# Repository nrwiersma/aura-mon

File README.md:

<picture>
  <source media="(prefers-color-scheme: dark)" srcset="http://svg.wiersma.co.za/github/project.v2?title=aura mon&tag=energy%20data%20logger&mode=dark">
  <source media="(prefers-color-scheme: light)" srcset="http://svg.wiersma.co.za/github/project.v2?title=aura mon&tag=energy%20data%20logger">
  
</picture>

`Aura Mon` is an RP2350-based energy data logger built around the tiny [SPM01](https://www.bituo-technik.com/product/spm01-flexible-1pn-63a/) Modbus meter. It samples power data over RS485, stores it on an SD card, and serves a local HTTP API and web UI over Ethernet.

## At a glance

* RP2350 microcontroller
* Modbus RTU over RS485 (SPM01)
* Ethernet for reliable network connectivity
* SD card logging and static web UI hosting
* RTC for timestamped data
* HTTP API with OTA updates and metrics

## System overview

## Data flow

## Why

The goal of this project is to create a reliable and easy-to-use energy data logger that can be used to monitor energy consumption in a home or small business. The SPM01 is a very affordable energy meter that can measure voltage, current, power, energy, and power factor while fitting in tight electrical panels.

## Quick start

1. Assemble the board and connect the SPM01 to the RS485 terminals.
2. Insert an SD card (required for logging).
3. Power the board with a regulated 5V supply on the screw terminals (or via USB-C with the jumper fitted for testing).
4. Connect Ethernet and find the device IP via your router's DHCP lease table.
5. Open `http://<device-ip>` to view the UI and use the API.

## Firmware

The firmware lives in `firmware/` and is written in C++ using the Arduino framework.

* Build/flash instructions: `firmware/FIRMWARE.md`
* HTTP API reference: `firmware/API.md`

### API highlights

* `GET /status` for live readings and runtime stats.
* `GET /energy` for CSV data export.
* `GET /logs` for log streaming.
* `GET`/`POST /config` for device configuration.
* `POST /ota` for firmware updates.
* `GET /metrics` for Prometheus-style metrics.

## Powering

The board can be powered using an external 5V power supply connected to the screw terminals. For testing purposes, it can also be powered via USB-C after connecting the onboard jumper.

## Safety

> [!WARNING]
> This project interfaces with mains-connected equipment. Only install it if you are qualified and follow local electrical safety requirements.

## Project status

The firmware and hardware are still in development and are only tested on the author's hardware. Expect rough edges and please report issues or improvements.

## Changelog

#### v0.1.0

* Initial schematic and board
* Initial firmware with basic functionality to read from the SPM01 and store data on the SD card

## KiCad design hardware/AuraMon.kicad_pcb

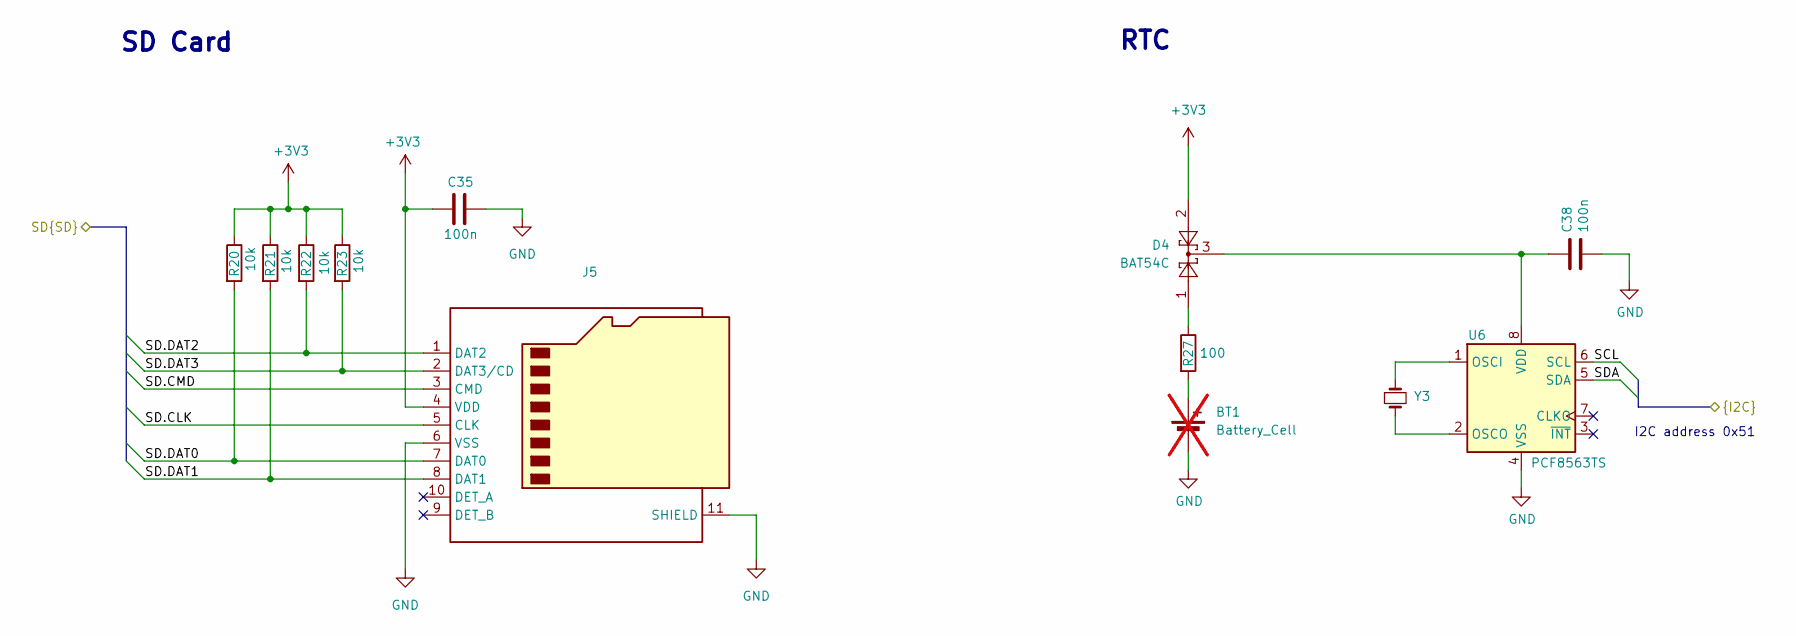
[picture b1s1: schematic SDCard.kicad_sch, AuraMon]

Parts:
BT1: Battery_Cell; BatteryHolder_Keystone_1060_1x2032; not fitted
C35, C38: 100n; C_0402_1005Metric; MPN CL05B104KO5NNNC; JLCPCB Part # C1525
D4: BAT54C; SOT-23; MPN BAT54C-7-F; JLCPCB Part # C134405
J5: Micro_SD_Card_Det_Hirose_DM3AT; AMPHENOL_1140084168; MPN 114-00841-68; JLCPCB Part # C3195424
R20, R21, R22, R23: 10k; R_0402_1005Metric; MPN RC0402JR-0710KL; JLCPCB Part # C60489
R27: 100; R_0402_1005Metric; MPN RC0402FR-07100RL; JLCPCB Part # C106232
U6: PCF8563TS; MSOP-8_3x3mm_P0.65mm; MPN PCF85063ATT/AJ; JLCPCB Part # C165608
Y3: X321532768KGD2SI; Crystal_SMD_3215-2Pin_3.2x1.5mm; MPN X321532768KGD2SI; JLCPCB Part # C620155

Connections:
+3V3: C35.2, D4.2, J5.4 (VDD), R20.1, R21.1, R22.1, R23.1; also elsewhere on the board
/MCU/SCL: U6.6 (SCL); also elsewhere on the board
/MCU/SD.CLK: J5.5 (CLK); also elsewhere on the board
/MCU/SD.CMD: J5.3 (CMD); also elsewhere on the board
/MCU/SD.DAT0: J5.7 (DAT0), R20.2; also elsewhere on the board
/MCU/SD.DAT1: J5.8 (DAT1), R21.2; also elsewhere on the board
/MCU/SD.DAT2: J5.1 (DAT2), R22.2; also elsewhere on the board
/MCU/SD.DAT3: J5.2 (DAT3/CD), R23.2; also elsewhere on the board
/MCU/SDA: U6.5 (SDA); also elsewhere on the board
GND: BT1.2 (-), C35.1, C38.2, J5.6 (VSS), J5.11 (SHIELD), U6.4 (VSS); also elsewhere on the board
unnamed: BT1.1 (+), R27.2
unnamed: D4.1, R27.1
unnamed: U6.1 (OSCI), Y3.1
unnamed: U6.2 (OSCO), Y3.2
unnamed: C38.1, D4.3, U6.8 (VDD)

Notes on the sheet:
I2C address 0x51
RTC
SD Card

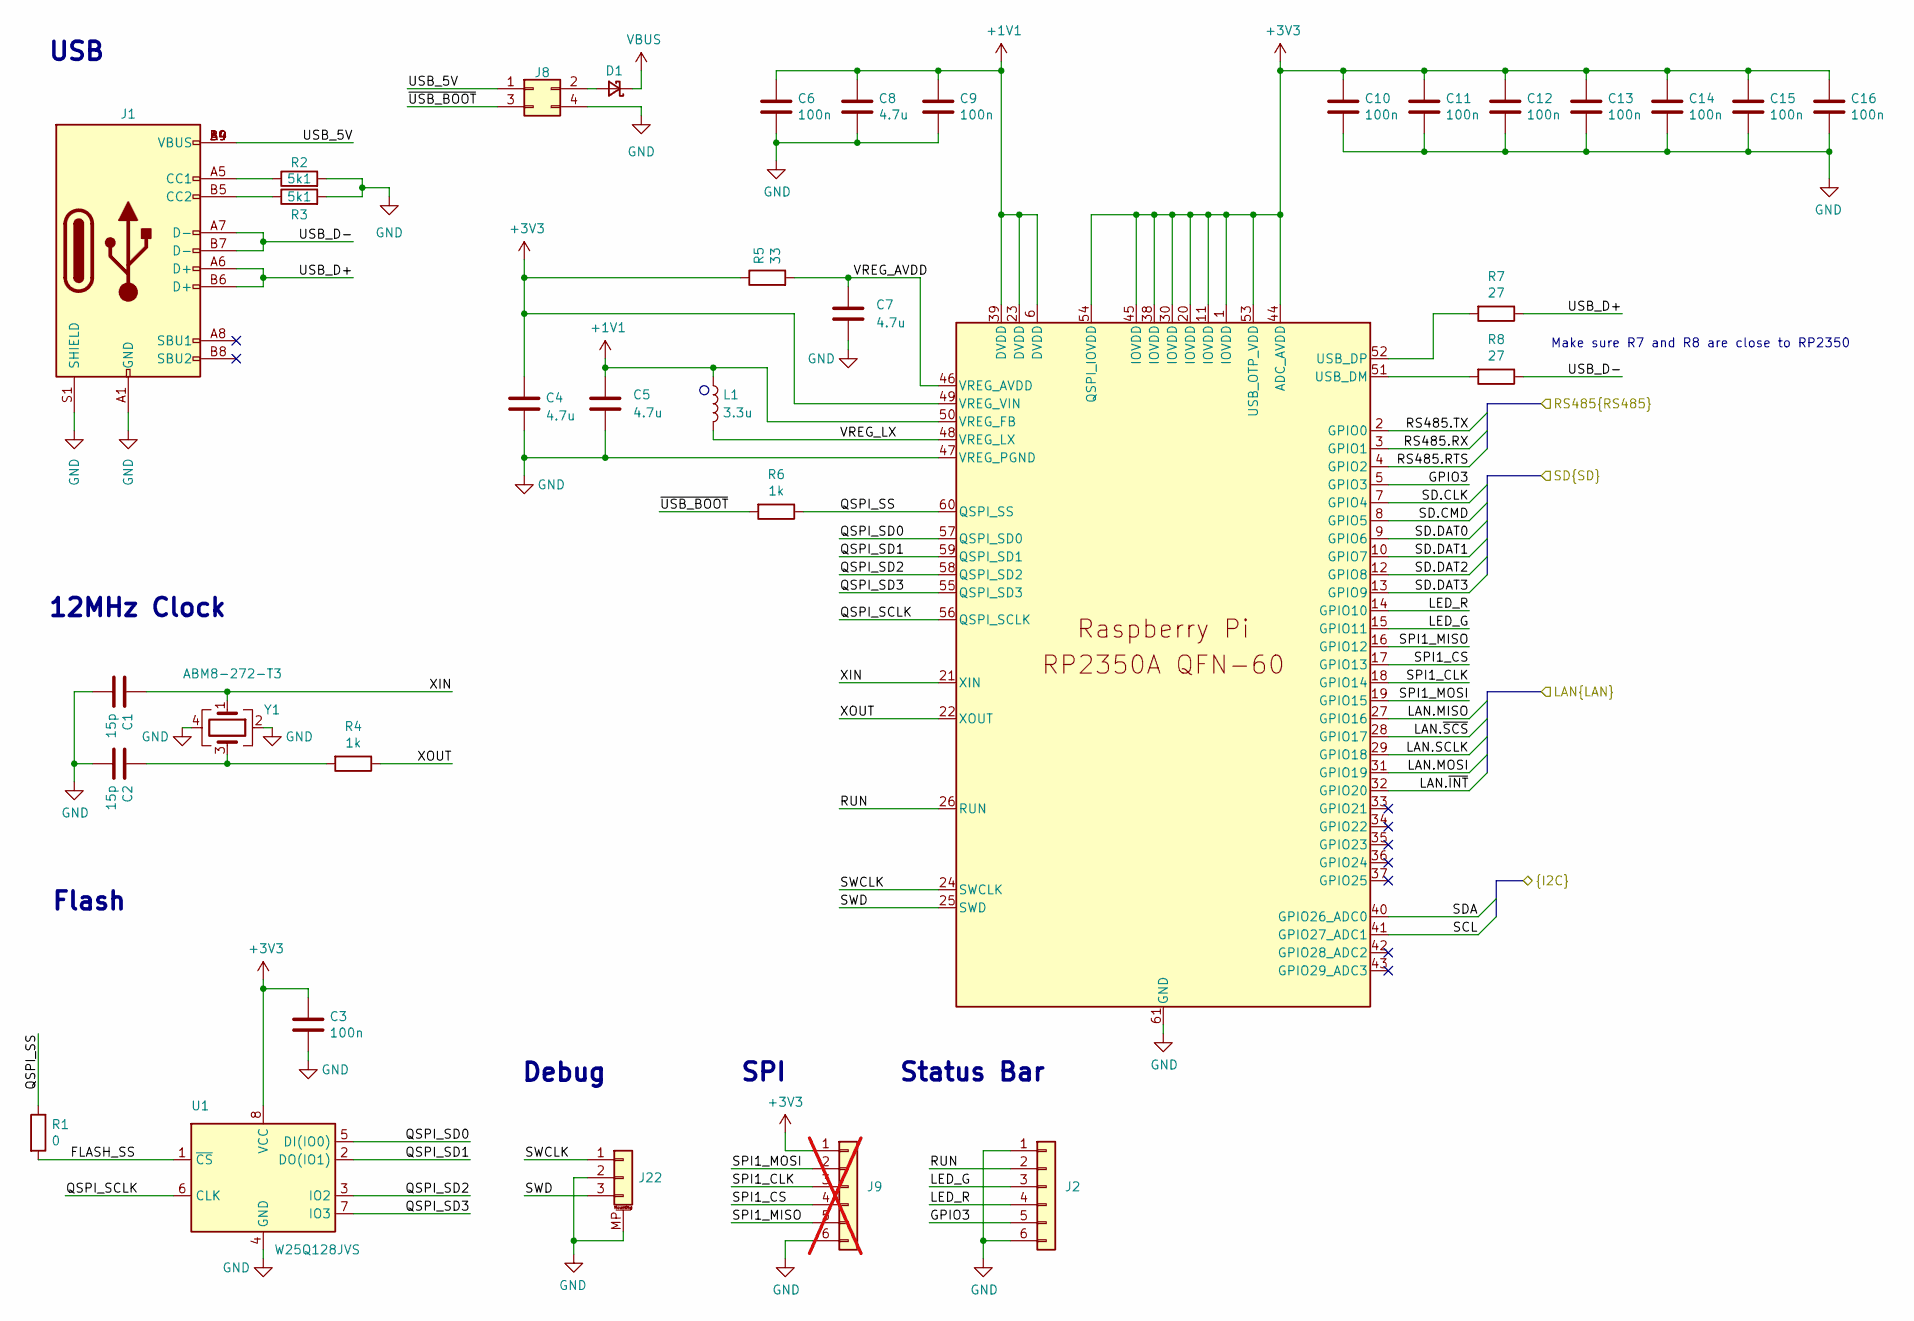
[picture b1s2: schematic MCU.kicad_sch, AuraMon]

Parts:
C1, C2: 15p; C_0402_1005Metric; MPN CL05C150JB5NNNC; JLCPCB Part # C86285
C3, C6, C9, C10, C11, C12, C13, C14, C15, C16: 100n; C_0402_1005Metric; MPN CL05B104KO5NNNC; JLCPCB Part # C1525
C4, C5: 4.7u; C_0402_1005Metric_small_pads; MPN CL05A475MO5NUNC; JLCPCB Part # C318563
C7, C8: 4.7u; C_0402_1005Metric; MPN CL05A475MO5NUNC; JLCPCB Part # C318563
D1: D_Schottky_Small; D_SOD-323; MPN BAT760-7; JLCPCB Part # C124187
J1: USB_C_Receptacle_USB2.0_16P; USB-C-SMD_TYPEC-305-ACP16H458; MPN TYPEC-305-ACP16H458; JLCPCB Part # C5454943
J2: Conn_01x06; JST_SH_BM06B-SRSS-TB_1x06-1MP_P1.00mm_Vertical; MPN BM06B-SRSS-TB(LF)(SN); JLCPCB Part # C160392
J8: Conn_02x02_Odd_Even; PinHeader_2x02_P1.27mm_Vertical; MPN DW127R-22-04-23; JLCPCB Part # C2935950
J9: Conn_01x06; JST_SUR_BM06B-SURS-TF_1x06-1MP_P0.80mm_Vertical; not fitted
J22: SM03B-SRSS-TB; JST_SH_SM03B-SRSS-TB_1x03-1MP_P1.00mm_Horizontal
L1: 3.3u; L_pol_2016; MPN AOTA-B201610S3R3-101-T; JLCPCB Part # C42411119
R1: 0; R_0402_1005Metric; MPN RC0402JR-070RL; JLCPCB Part # C60485
R2, R3: 5k1; R_0402_1005Metric; MPN RC0402FR-075K1L; JLCPCB Part # C105872
R4, R6: 1k; R_0402_1005Metric; MPN RC0402FR-071KL; JLCPCB Part # C106235
R5: 33; R_0402_1005Metric; MPN RC0402FR-0733RL; JLCPCB Part # C138002
R7, R8: 27; R_0402_1005Metric; MPN RC0402FR-0727RL; JLCPCB Part # C138021
U1: W25Q128JVS; SOIC-8_5.23x5.23mm_P1.27mm; MPN W25Q128JVSIQ; JLCPCB Part # C97521
U2: RP2350A; QFN-60_7X7_RPI; MPN RP2350A; JLCPCB Part # C42411118
Y1: ABM8-272-T3; Crystal_SMD_3225-4Pin_3.2x2.5mm; MPN ABM8-272-T3; JLCPCB Part # C20625731

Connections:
+1V1: C5.1, C6.1, C8.1, C9.1, L1.1, U2.6 (DVDD), U2.23 (DVDD), U2.39 (DVDD), U2.50 (VREG_FB)
+3V3: C3.1, C4.1, C10.1, C11.1, C12.1, C13.1, C14.1, C15.1, C16.1, J9.1, R5.1, U1.8 (VCC), U2.1 (IOVDD), U2.11 (IOVDD), U2.20 (IOVDD), U2.30 (IOVDD), U2.38 (IOVDD), U2.44 (ADC_AVDD), U2.45 (IOVDD), U2.49 (VREG_VIN), U2.53 (USB_OTP_VDD), U2.54 (QSPI_IOVDD); also elsewhere on the board
/LAN/LAN.MISO: U2.27 (GPIO16); also elsewhere on the board
/LAN/LAN.MOSI: U2.31 (GPIO19); also elsewhere on the board
/LAN/LAN.SCLK: U2.29 (GPIO18); also elsewhere on the board
/LAN/LAN.~INT: U2.32 (GPIO20); also elsewhere on the board
/LAN/LAN.~SCS: U2.28 (GPIO17); also elsewhere on the board
/MCU/FLASH_SS: R1.2, U1.1 (~CS)
/MCU/GPIO3: J2.5, U2.5 (GPIO3)
/MCU/LED_G: J2.3, U2.15 (GPIO11)
/MCU/LED_R: J2.4, U2.14 (GPIO10)
/MCU/QSPI_SCLK: U1.6 (CLK), U2.56 (QSPI_SCLK)
/MCU/QSPI_SD0: U1.5 (DI(IO0)), U2.57 (QSPI_SD0)
/MCU/QSPI_SD1: U1.2 (DO(IO1)), U2.59 (QSPI_SD1)
/MCU/QSPI_SD2: U1.3 (IO2), U2.58 (QSPI_SD2)
/MCU/QSPI_SD3: U1.7 (IO3), U2.55 (QSPI_SD3)
/MCU/QSPI_SS: R1.1, R6.1, U2.60 (QSPI_SS)
/MCU/RS485.RTS: U2.4 (GPIO2); also elsewhere on the board
/MCU/RS485.RX: U2.3 (GPIO1); also elsewhere on the board
/MCU/RS485.TX: U2.2 (GPIO0); also elsewhere on the board
/MCU/RUN: J2.2, U2.26 (RUN)
/MCU/SCL: U2.41 (GPIO27_ADC1); also elsewhere on the board
/MCU/SD.CLK: U2.7 (GPIO4); also elsewhere on the board
/MCU/SD.CMD: U2.8 (GPIO5); also elsewhere on the board
/MCU/SD.DAT0: U2.9 (GPIO6); also elsewhere on the board
/MCU/SD.DAT1: U2.10 (GPIO7); also elsewhere on the board
/MCU/SD.DAT2: U2.12 (GPIO8); also elsewhere on the board
/MCU/SD.DAT3: U2.13 (GPIO9); also elsewhere on the board
/MCU/SDA: U2.40 (GPIO26_ADC0); also elsewhere on the board
/MCU/SPI1_CLK: J9.3, U2.18 (GPIO14)
/MCU/SPI1_CS: J9.4, U2.17 (GPIO13)
/MCU/SPI1_MISO: J9.5, U2.16 (GPIO12)
/MCU/SPI1_MOSI: J9.2, U2.19 (GPIO15)
/MCU/SWCLK: J22.1, U2.24 (SWCLK)
/MCU/SWD: J22.3, U2.25 (SWD)
/MCU/USB_5V: J1.A4 (VBUS), J1.A9 (VBUS), J1.B4 (VBUS), J1.B9 (VBUS), J8.1
/MCU/USB_D+: J1.A6 (D+), J1.B6 (D+), R7.1
/MCU/USB_D-: J1.A7 (D-), J1.B7 (D-), R8.1
/MCU/VREG_AVDD: C7.1, R5.2, U2.46 (VREG_AVDD)
/MCU/VREG_LX: L1.2, U2.48 (VREG_LX)
/MCU/XIN: C1.1, U2.21 (XIN), Y1.1
/MCU/XOUT: R4.1, U2.22 (XOUT)
/MCU/~USB_BOOT: J8.3, R6.2
GND: C1.2, C2.2, C3.2, C4.2, C5.2, C6.2, C7.2, C8.2, C9.2, C10.2, C11.2, C12.2, C13.2, C14.2, C15.2, C16.2, J1.A1 (GND), J1.A12 (GND), J1.B1 (GND), J1.B12 (GND), J1.S1 (SHIELD), J2.1, J2.6, J8.4, J9.6, J22.2, J22.MP (MountPin), R2.2, R3.2, U1.4 (GND), U2.47 (VREG_PGND), U2.61 (GND), Y1.2, Y1.4; also elsewhere on the board
unnamed: C2.1, R4.2, Y1.3
unnamed: D1.2 (A), J8.2
unnamed: J1.A5 (CC1), R2.1
unnamed: J1.B5 (CC2), R3.1
unnamed: R8.2, U2.51 (USB_DM)
unnamed: R7.2, U2.52 (USB_DP)
VBUS: D1.1 (K); also elsewhere on the board

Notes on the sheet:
Debug
Status Bar
USB
Make sure R7 and R8 are close to RP2350
SPI
12MHz Clock
Flash

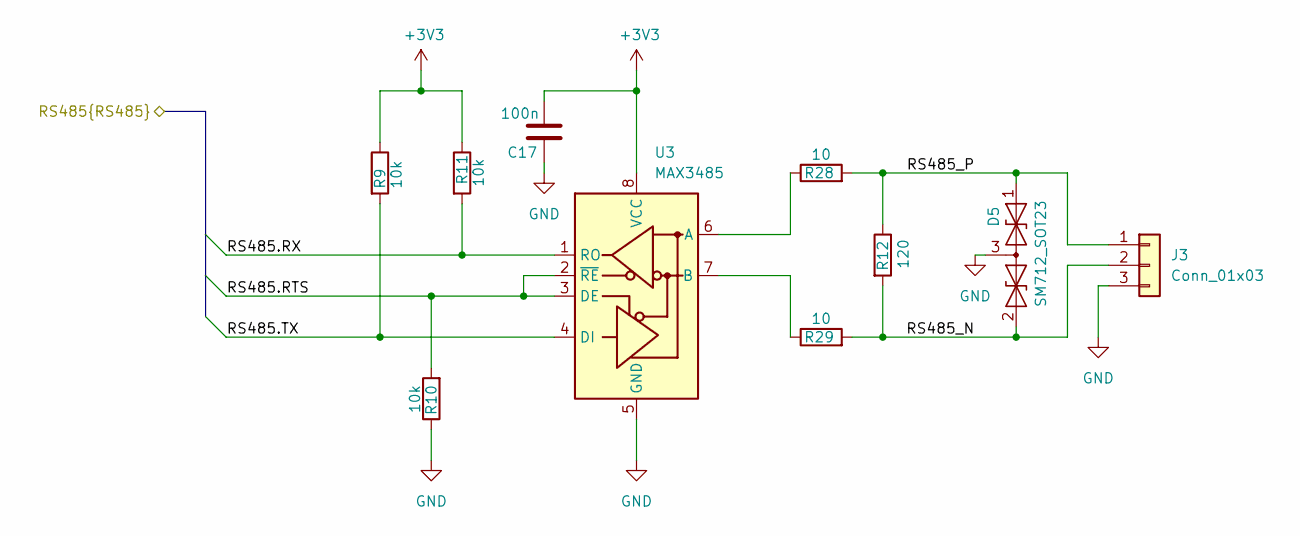
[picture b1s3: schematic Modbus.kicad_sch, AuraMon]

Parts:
C17: 100n; C_0402_1005Metric; MPN CL05B104KO5NNNC; JLCPCB Part # C1525
D5: SM712_SOT23; SOT-23; MPN CDSOT23-SM712; JLCPCB Part # C404012
J3: Conn_01x03; JST_PH_S3B-PH-K_1x03_P2.00mm_Horizontal; MPN S3B-PH-K-S(LF)(SN); JLCPCB Part # C157929
R9, R10, R11: 10k; R_0402_1005Metric; MPN RC0402JR-0710KL; JLCPCB Part # C60489
R12: 120; R_0402_1005Metric; MPN RC0402FR-07120RL; JLCPCB Part # C114758
R28, R29: 10; R_0402_1005Metric; MPN RC0402FR-0710RL; JLCPCB Part # C138066
U3: MAX3485; SOIC-8; MPN SN65HVD75DR; JLCPCB Part # C57928

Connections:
+3V3: C17.2, R9.1, R11.1, U3.8 (VCC); also elsewhere on the board
/MCU/RS485.RTS: R10.2, U3.2 (~RE), U3.3 (DE); also elsewhere on the board
/MCU/RS485.RX: R11.2, U3.1 (RO); also elsewhere on the board
/MCU/RS485.TX: R9.2, U3.4 (DI); also elsewhere on the board
/Modbus/RS485_N: D5.2 (A2), J3.2, R12.2, R29.2
/Modbus/RS485_P: D5.1 (A1), J3.1, R12.1, R28.2
GND: C17.1, D5.3 (common), J3.3, R10.1, U3.5 (GND); also elsewhere on the board
unnamed: R28.1, U3.6 (A)
unnamed: R29.1, U3.7 (B)

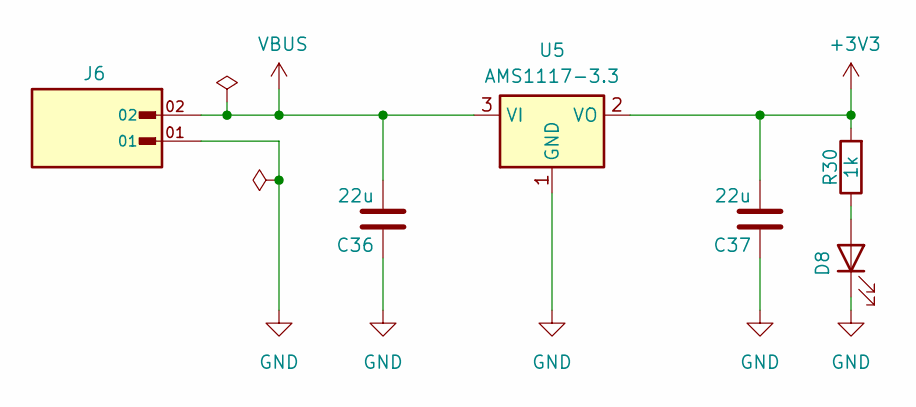
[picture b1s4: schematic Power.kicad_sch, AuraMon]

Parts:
C36, C37: 22u; C_0603_1608Metric; MPN CL10A226MQ8NRNC; JLCPCB Part # C59461
D8: LED; LED_0603_1608Metric; MPN LTST-C191KGKT; JLCPCB Part # C125098
J6: 1881448; PHOENIX_1881448; MPN 1881448; JLCPCB Part # C5480444
R30: 1k; R_0402_1005Metric; MPN RC0402FR-071KL; JLCPCB Part # C106235
U5: AMS1117-3.3; SOT-223-3_TabPin2; MPN AMS1117-3.3; JLCPCB Part # C347222

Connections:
+3V3: C37.2, R30.2, U5.2 (VO); also elsewhere on the board
GND: C36.1, C37.1, D8.1 (K), J6.01, U5.1 (GND); also elsewhere on the board
unnamed: D8.2 (A), R30.1
VBUS: C36.2, J6.02, U5.3 (VI); also elsewhere on the board

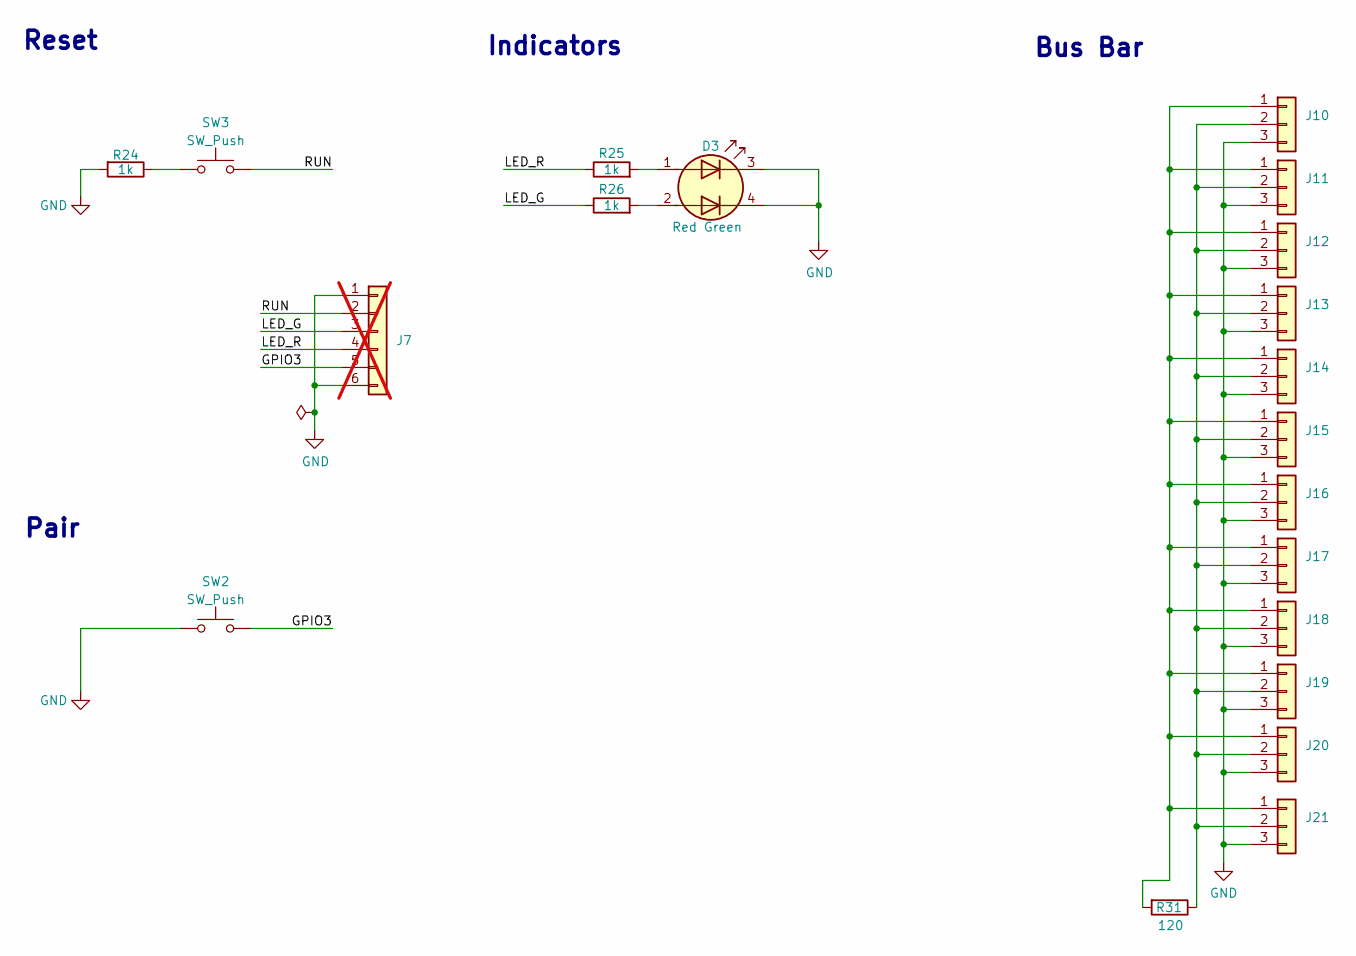
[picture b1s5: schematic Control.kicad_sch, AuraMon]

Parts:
D3: Red Green; LED_LiteOn_LTST-C295K_1.6x0.8mm; MPN LTST-C295KGKRKT; JLCPCB Part # C364568
J7: Conn_01x06; JST_SH_BM06B-SRSS-TB_1x06-1MP_P1.00mm_Vertical; MPN BM06B-SRSS-TB(LF)(SN); JLCPCB Part # C160392; not fitted
J10, J11, J12, J13, J14, J15, J16, J17, J18, J19, J20, J21: Conn_01x03; JST_PH_B3B-PH-K_1x03_P2.00mm_Vertical; MPN B3B-PH-K-S(LF)(SN); JLCPCB Part # C131339
R24, R25, R26: 1k; R_0402_1005Metric; MPN RC0402FR-071KL; JLCPCB Part # C106235
R31: 120; R_0402_1005Metric; MPN RC0402FR-07120RL; JLCPCB Part # C114758
SW2, SW3: SW_Push; PTS815SJM250SMTRLFS; MPN SKRPACE010; JLCPCB Part # C139797

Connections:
/Control/GPIO3: J7.5, SW2.2
/Control/LED_G: J7.3, R26.1
/Control/LED_R: J7.4, R25.1
/Control/RUN: J7.2, SW3.2
GND: D3.3 (K1), D3.4 (K2), J7.1, J7.6, J10.3, J11.3, J12.3, J13.3, J14.3, J15.3, J16.3, J17.3, J18.3, J19.3, J20.3, J21.3, R24.2, SW2.1; also elsewhere on the board
unnamed: D3.1 (A1), R25.2
unnamed: D3.2 (A2), R26.2
unnamed: J10.1, J11.1, J12.1, J13.1, J14.1, J15.1, J16.1, J17.1, J18.1, J19.1, J20.1, J21.1, R31.2
unnamed: J10.2, J11.2, J12.2, J13.2, J14.2, J15.2, J16.2, J17.2, J18.2, J19.2, J20.2, J21.2, R31.1
unnamed: R24.1, SW3.1

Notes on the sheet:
Indicators
Bus Bar
Pair
Reset

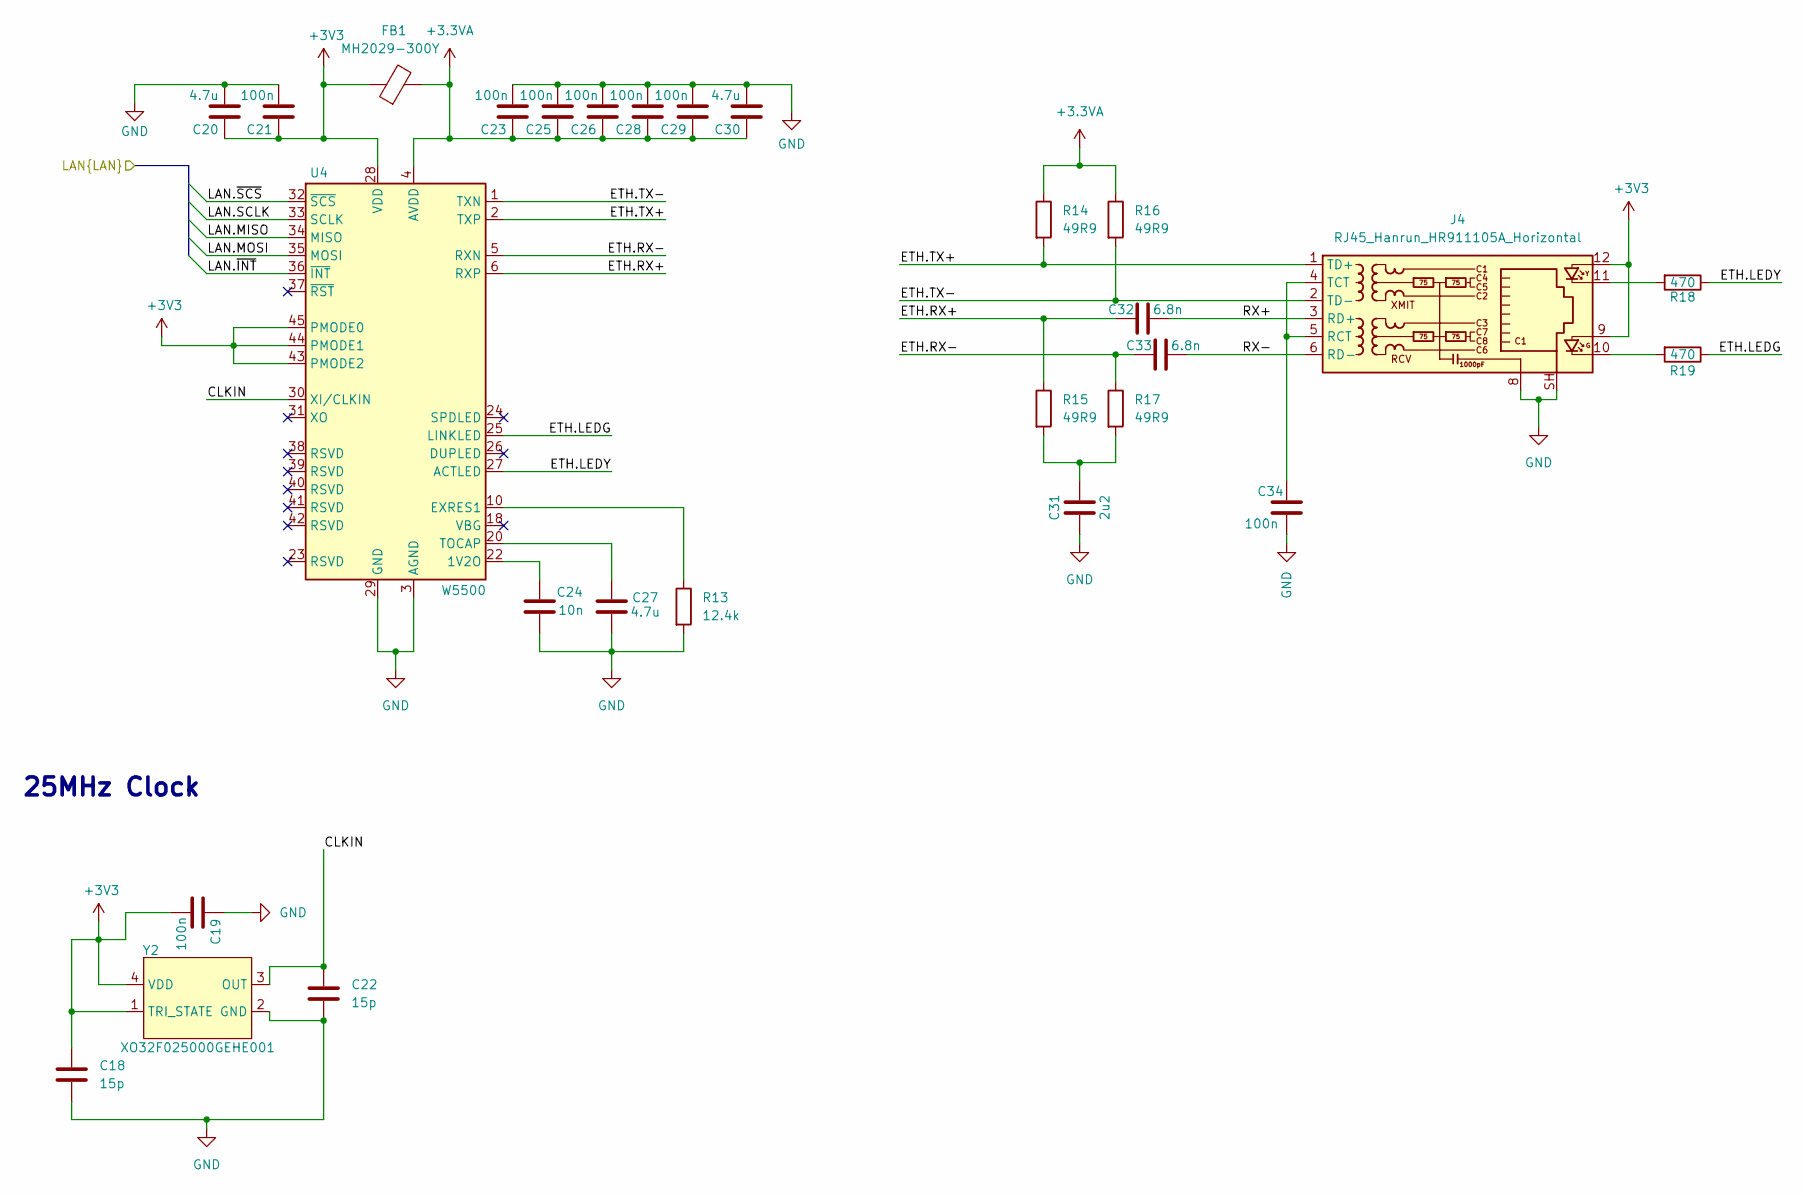
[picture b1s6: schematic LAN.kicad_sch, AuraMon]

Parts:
C18, C22: 15p; C_0402_1005Metric; MPN CL05C150JB5NNNC; JLCPCB Part # C86285
C19, C21, C23, C25, C26, C28, C29, C34: 100n; C_0402_1005Metric; MPN CL05B104KO5NNNC; JLCPCB Part # C1525
C20, C27, C30: 4.7u; C_0402_1005Metric; MPN CL05A475MO5NUNC; JLCPCB Part # C318563
C24: 10n; C_0402_1005Metric; MPN CL05B103KB5NNNC; JLCPCB Part # C15195
C31: 2u2; C_0402_1005Metric; MPN CL05A225KA5NUNC; JLCPCB Part # C307418
C32, C33: 6.8n; C_0603_1608Metric; MPN CC0603KRX7R0BB682; JLCPCB Part # C576854
FB1: MH2029-300Y; L0805; MPN MH2029-300Y; JLCPCB Part # C840593
J4: RJ45_Hanrun_HR911105A_Horizontal; MPN HR911105A; JLCPCB Part # C12074
R13: 12.4k; R_0603_1608Metric; MPN RC0603FR-0712K4L; JLCPCB Part # C137798
R14, R15, R16, R17: 49R9; R_0603_1608Metric; MPN RC0603FR-0749R9L; JLCPCB Part # C114625
R18, R19: 470; R_0402_1005Metric; MPN RC0402FR-7W470RL; JLCPCB Part # C606172
U4: W5500; LQFP-48_7x7mm_P0.5mm; MPN W5500; JLCPCB Part # C32843
Y2: XO32F025000GEHE001; Crystal_SMD_3225-4Pin_3.2x2.5mm; MPN XO32F025000GEHE001; JLCPCB Part # C20607963

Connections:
+3.3VA: C23.1, C25.1, C26.1, C28.1, C29.1, C30.1, FB1.2, R14.1, R16.1, U4.4 (AVDD), U4.8 (AVDD), U4.11 (AVDD), U4.15 (AVDD), U4.17 (AVDD), U4.21 (AVDD)
+3V3: C18.2, C19.2, C20.1, C21.1, FB1.1, J4.9, J4.12, U4.28 (VDD), U4.43 (PMODE2), U4.44 (PMODE1), U4.45 (PMODE0), Y2.1 (TRI_STATE), Y2.4 (VDD); also elsewhere on the board
/LAN/CLKIN: C22.1, U4.30 (XI/CLKIN), Y2.3 (OUT)
/LAN/ETH.LEDG: R19.1, U4.25 (LINKLED)
/LAN/ETH.LEDY: R18.1, U4.27 (ACTLED)
/LAN/ETH.RX+: C32.1, R15.1, U4.6 (RXP)
/LAN/ETH.RX-: C33.1, R17.1, U4.5 (RXN)
/LAN/ETH.TX+: J4.1 (TD+), R14.2, U4.2 (TXP)
/LAN/ETH.TX-: J4.2 (TD-), R16.2, U4.1 (TXN)
/LAN/LAN.MISO: U4.34 (MISO); also elsewhere on the board
/LAN/LAN.MOSI: U4.35 (MOSI); also elsewhere on the board
/LAN/LAN.SCLK: U4.33 (SCLK); also elsewhere on the board
/LAN/LAN.~INT: U4.36 (~INT); also elsewhere on the board
/LAN/LAN.~SCS: U4.32 (~SCS); also elsewhere on the board
/LAN/RX+: C32.2, J4.3 (RD+)
/LAN/RX-: C33.2, J4.6 (RD-)
GND: C18.1, C19.1, C20.2, C21.2, C22.2, C23.2, C24.2, C25.2, C26.2, C27.2, C28.2, C29.2, C30.2, C31.2, C34.2, J4.8, J4.SH, R13.2, U4.3 (AGND), U4.9 (AGND), U4.14 (AGND), U4.16 (AGND), U4.19 (AGND), U4.29 (GND), U4.48 (AGND), Y2.2 (GND); also elsewhere on the board
unnamed: C31.1, R15.2, R17.2
unnamed: J4.10, R19.2
unnamed: J4.11, R18.2
unnamed: C34.1, J4.4 (TCT), J4.5 (RCT)
unnamed: C24.1, U4.22 (1V2O)
unnamed: R13.1, U4.10 (EXRES1)
unnamed: C27.1, U4.20 (TOCAP)

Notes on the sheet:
25MHz Clock

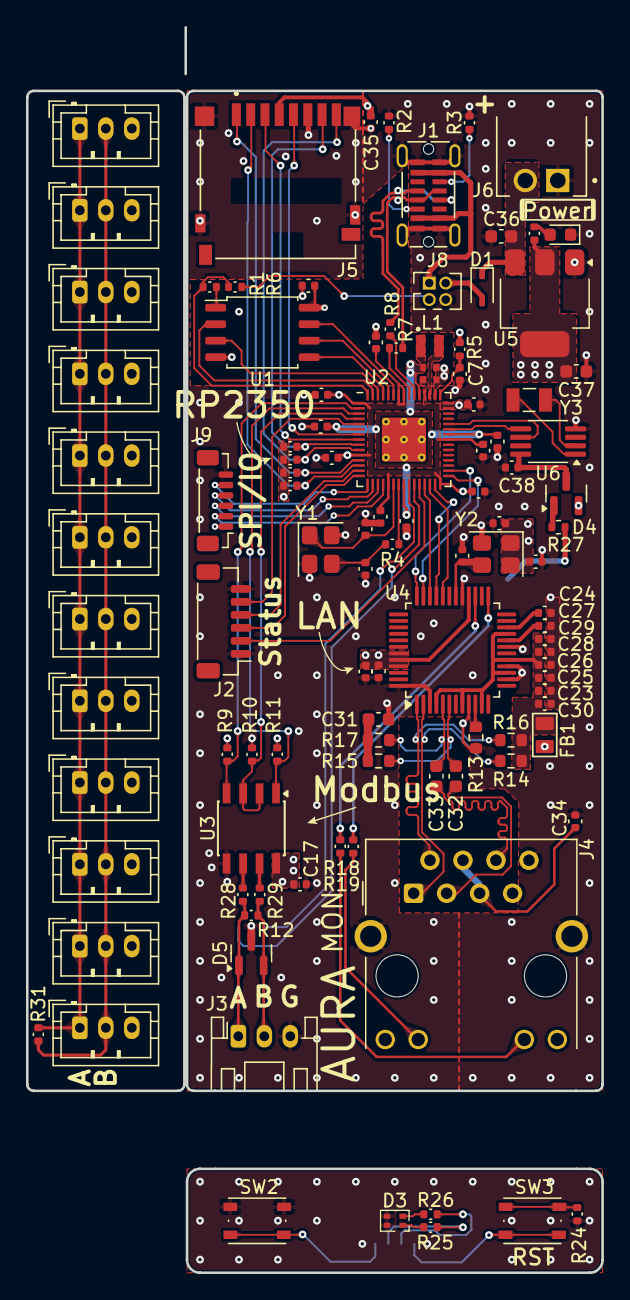
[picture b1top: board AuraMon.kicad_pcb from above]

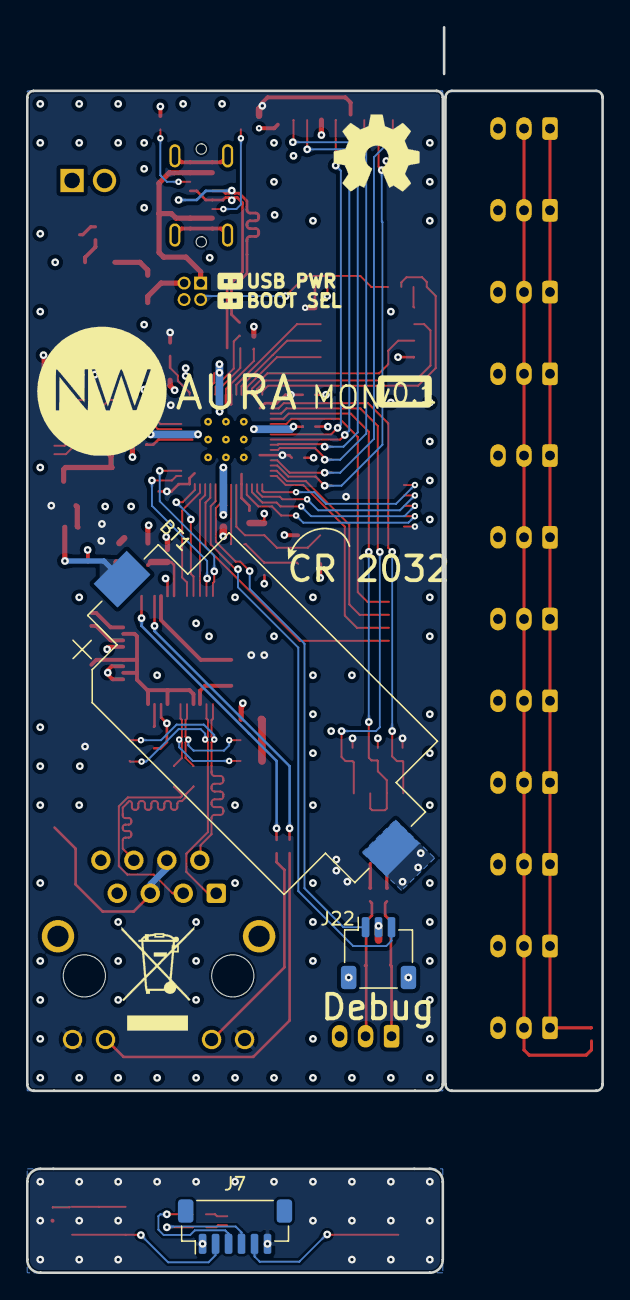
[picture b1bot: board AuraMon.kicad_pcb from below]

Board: 4 copper layers, 44.3 x 95.9 mm, 117 parts (7 on the bottom side), 87 nets.

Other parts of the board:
G2, G2#2: LOGO; Arrow2
G3: LOGO; Arrow3
G4: LOGO; Arrow1
G10: LOGO; Logo
OSHW: OSHW-Symbol_6.7x6mm_SilkScreen
SS3: WEEE-Logo_5.6x8mm_SilkScreen

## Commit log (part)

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2025-08-16 chore: initial commit
2025-09-25 feat: initial PCB
2025-09-27 feat: initial PCB (#1)
2025-09-27 fix: unavailable components
2025-09-28 feat: replace status LED
2025-09-28 wip: first test
2025-10-02 wip: add RTC and input devices
2025-10-10 feat: logger
2025-10-10 fix: logger levels
2025-10-17 wip: freertos
2025-10-18 fix: status LED resistor value
2025-10-19 wip: sdcard and logger works
2025-10-20 fix: update arduino-pico to fix eth
2025-11-12 feat: add SWD footprint
2026-01-16 chore: add readme
2026-01-16 chore: add change log
2026-01-16 chore: add readme (#2)
2026-01-16 fix: RTC
2026-01-16 wip: task queue working
2026-01-16 wip: minor changes
2026-01-16 wip: minor fixes
2026-01-16 wip: data logger done
2026-01-16 feat: add extract, fix hzHrs
2026-01-16 feat: working data log
2026-01-16 wip: add API
2026-01-16 fix: gitignore
2026-01-23 remove commented code
2026-01-23 feat: add datalog tests
2026-01-24 feat: add config parsing
2026-01-24 feat: add config tests
2026-01-24 feat: add proper errors
2026-01-25 feat: add device syncing
2026-01-27 feat: load network config
2026-01-27 fix: use proper errors in datalog
2026-01-28 wip: energy api
2026-01-28 chore: fix platform version
2026-01-29 fix: minor issues
2026-01-29 feat: add config endpoints
2026-01-29 feat: add logs endpoint
2026-02-05 feat: add status
2026-02-06 chore: setup core1 correctly
2026-02-06 feat: add versioning
2026-02-08 feat: add ota
2026-02-08 feat: add frontend
2026-02-08 feat: support gzip files
2026-02-08 feat: add OTA to the frontend
2026-02-08 feat: add public upload
2026-02-08 feat: dark mode
2026-02-08 feat(ui): use sliders instead of checkboxes
2026-02-09 feat: add device actions
2026-02-09 feat: switch to preact framework
2026-02-09 feat: update ui table
2026-02-10 feat: add watchdog
2026-02-10 feat: add metrics endpoint
2026-02-12 fix: issue with loading js
2026-02-12 feat: handle button press
2026-02-13 fix: limit energy response rows
2026-02-13 feat: add documentation
2026-02-13 feat: add workflow
2026-02-13 fix: min C++ version
2026-02-13 fix: tests
2026-02-13 fix: workflow
2026-02-13 fix: C++ install
2026-02-13 test: find failing test
2026-02-13 fix: test failure
2026-02-13 fix: skip workflow build
2026-02-13 feat: initial firmware (#3)
2026-02-14 feat: allow log endpoint start bytes
2026-02-14 feat: allow log limit
2026-02-14 feat: allow log endpoint start and limit bytes (#4)
2026-02-14 fix: update topbar
2026-02-15 feat: add hz to energy output
2026-02-15 feat: add hz to energy output (#5)
2026-02-15 fix: update topbar (#6)
2026-02-16 feat: update dark mode theme
2026-02-17 fix: drawer close button
2026-02-17 feat: update dark mode theme (#7)
    * feat: update dark mode theme
    * fix: drawer close button
2026-02-17 fix: UI drawer button
2026-02-17 fix: minor fixes
2026-02-17 fix: minor fixes (#8)
2026-02-17 feat: add favicon
2026-02-17 feat: handle ico extnesions
2026-02-18 feat: increase precision of wh
2026-02-19 feat: add additional info to metrics and stats
2026-02-19 feat: add additional info to metrics and stats (#9)
2026-02-19 feat: track datalog cache hits
2026-02-19 feat: add additional info to UI
2026-02-19 feat: add device reboot
2026-02-19 feat: refactor icons
2026-02-19 feat: add reboot endpoint (#10)
    * feat: add device reboot
    * feat: refactor icons
2026-02-21 fix: reboot url
2026-02-27 feat: better startup sequencing
2026-03-01 chore: firmware diagram
2026-03-01 fix issues
2026-03-01 refactor
2026-03-01 chore: firmware diagram (#11)
2026-03-06 bugfix
2026-03-08 more fix
2026-03-08 fix: include casing
2026-03-08 fix: minor issues and improvements (#12)
2026-03-08 chore: update README
2026-03-08 chore: update README (#13)
2026-03-08 chore: add github assets
2026-03-08 chore: add github assets (#14)
2026-03-13 fix: various issues
2026-03-13 test: logger
2026-03-13 test: multiple tests
2026-03-13 chore: refactor test stubs
2026-03-13 fix: various bugs (#15)
2026-03-18 feat: add crash handler and restart reason
2026-03-18 feat: add crash handler and restart reason (#16)
2026-03-18 fix: remove watchdog trigger
2026-03-18 fix: remove watchdog trigger (#17)
2026-03-18 feat: add log truncation
2026-03-18 feat: add log truncation (#18)
2026-03-18 fix: missing log removal
2026-03-18 fix: missing log removal (#19)
2026-03-18 feat: minor improvements
2026-03-18 fix: minor issue with locking in data corruption
2026-03-18 fix: edge case issues
2026-03-19 feat: switch to string
2026-03-19 feat: minor improvements (#20)
2026-03-19 feat: refactor devices
2026-03-20 feat: reaftor naming
2026-03-20 feat: refactor error to expected
2026-03-20 feat: refactor SD to file thread safe
2026-03-20 feat: refactor the codebase (#21)
2026-03-20 feat: better metrics
2026-03-20 feat: better metrics (#22)
2026-03-20 chore: consistent formatting
2026-03-21 refactor: rename source files to snake_case
2026-03-21 chore: consistent formatting (#23)
2026-03-21 fix: crash handler
2026-03-21 fix: crash handler (#24)
2026-03-22 fix: stop watchdog reset if crashed
2026-03-23 feat: refactor the logger
2026-03-23 feat: refactor the logger (#26)
2026-04-05 fix: premature read from sd
2026-04-05 fix: premature read from sd (#27)
2026-04-05 fix: bad mutex enter
2026-04-05 fix: bad mutex enter (#28)
2026-04-05 fix: log for ts
2026-04-05 fix: log for ts (#29)
2026-04-06 feat: fix memory leak
2026-04-06 feat: fix memory leak (#30)
2026-04-06 fix: cleanup time logging
2026-04-06 fix: cleanup time logging (#31)
2026-04-06 feat: add more metrics
2026-04-06 fix: time adjustment
2026-04-06 feat: add more metrics (#32)
    * feat: add more metrics
    * fix: time adjustment
2026-04-06 fix: crash in config
2026-04-06 fix: crash in config (#33)
2026-04-06 fix: cleanly close SD card on reboot
2026-04-06 fix: cleanly close SD card on reboot (#34)
2026-04-06 fix: minor issues (#35)
2026-04-07 chore: minor grafana board updates
2026-04-07 fix: properly get the ntp srv size
2026-04-07 fix: properly get the ntp srv size (#36)
2026-05-30 fix: occational lockup in write path
2026-05-30 fix: occational lockup in write path (#37)
2026-06-21 chore(deps): bump actions/checkout from 6 to 7 in the all group
    Bumps the all group with 1 update: [actions/checkout](https://github.com/actions/checkout).
    Updates `actions/checkout` from 6 to 7
    - [Release notes](https://github.com/actions/checkout/releases)
    - [Changelog](https://github.com/actions/checkout/blob/main/CHANGELOG.md)
    - [Commits](https://github.com/actions/checkout/compare/v6...v7)
    ---

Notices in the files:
README.md:
License: MIT
